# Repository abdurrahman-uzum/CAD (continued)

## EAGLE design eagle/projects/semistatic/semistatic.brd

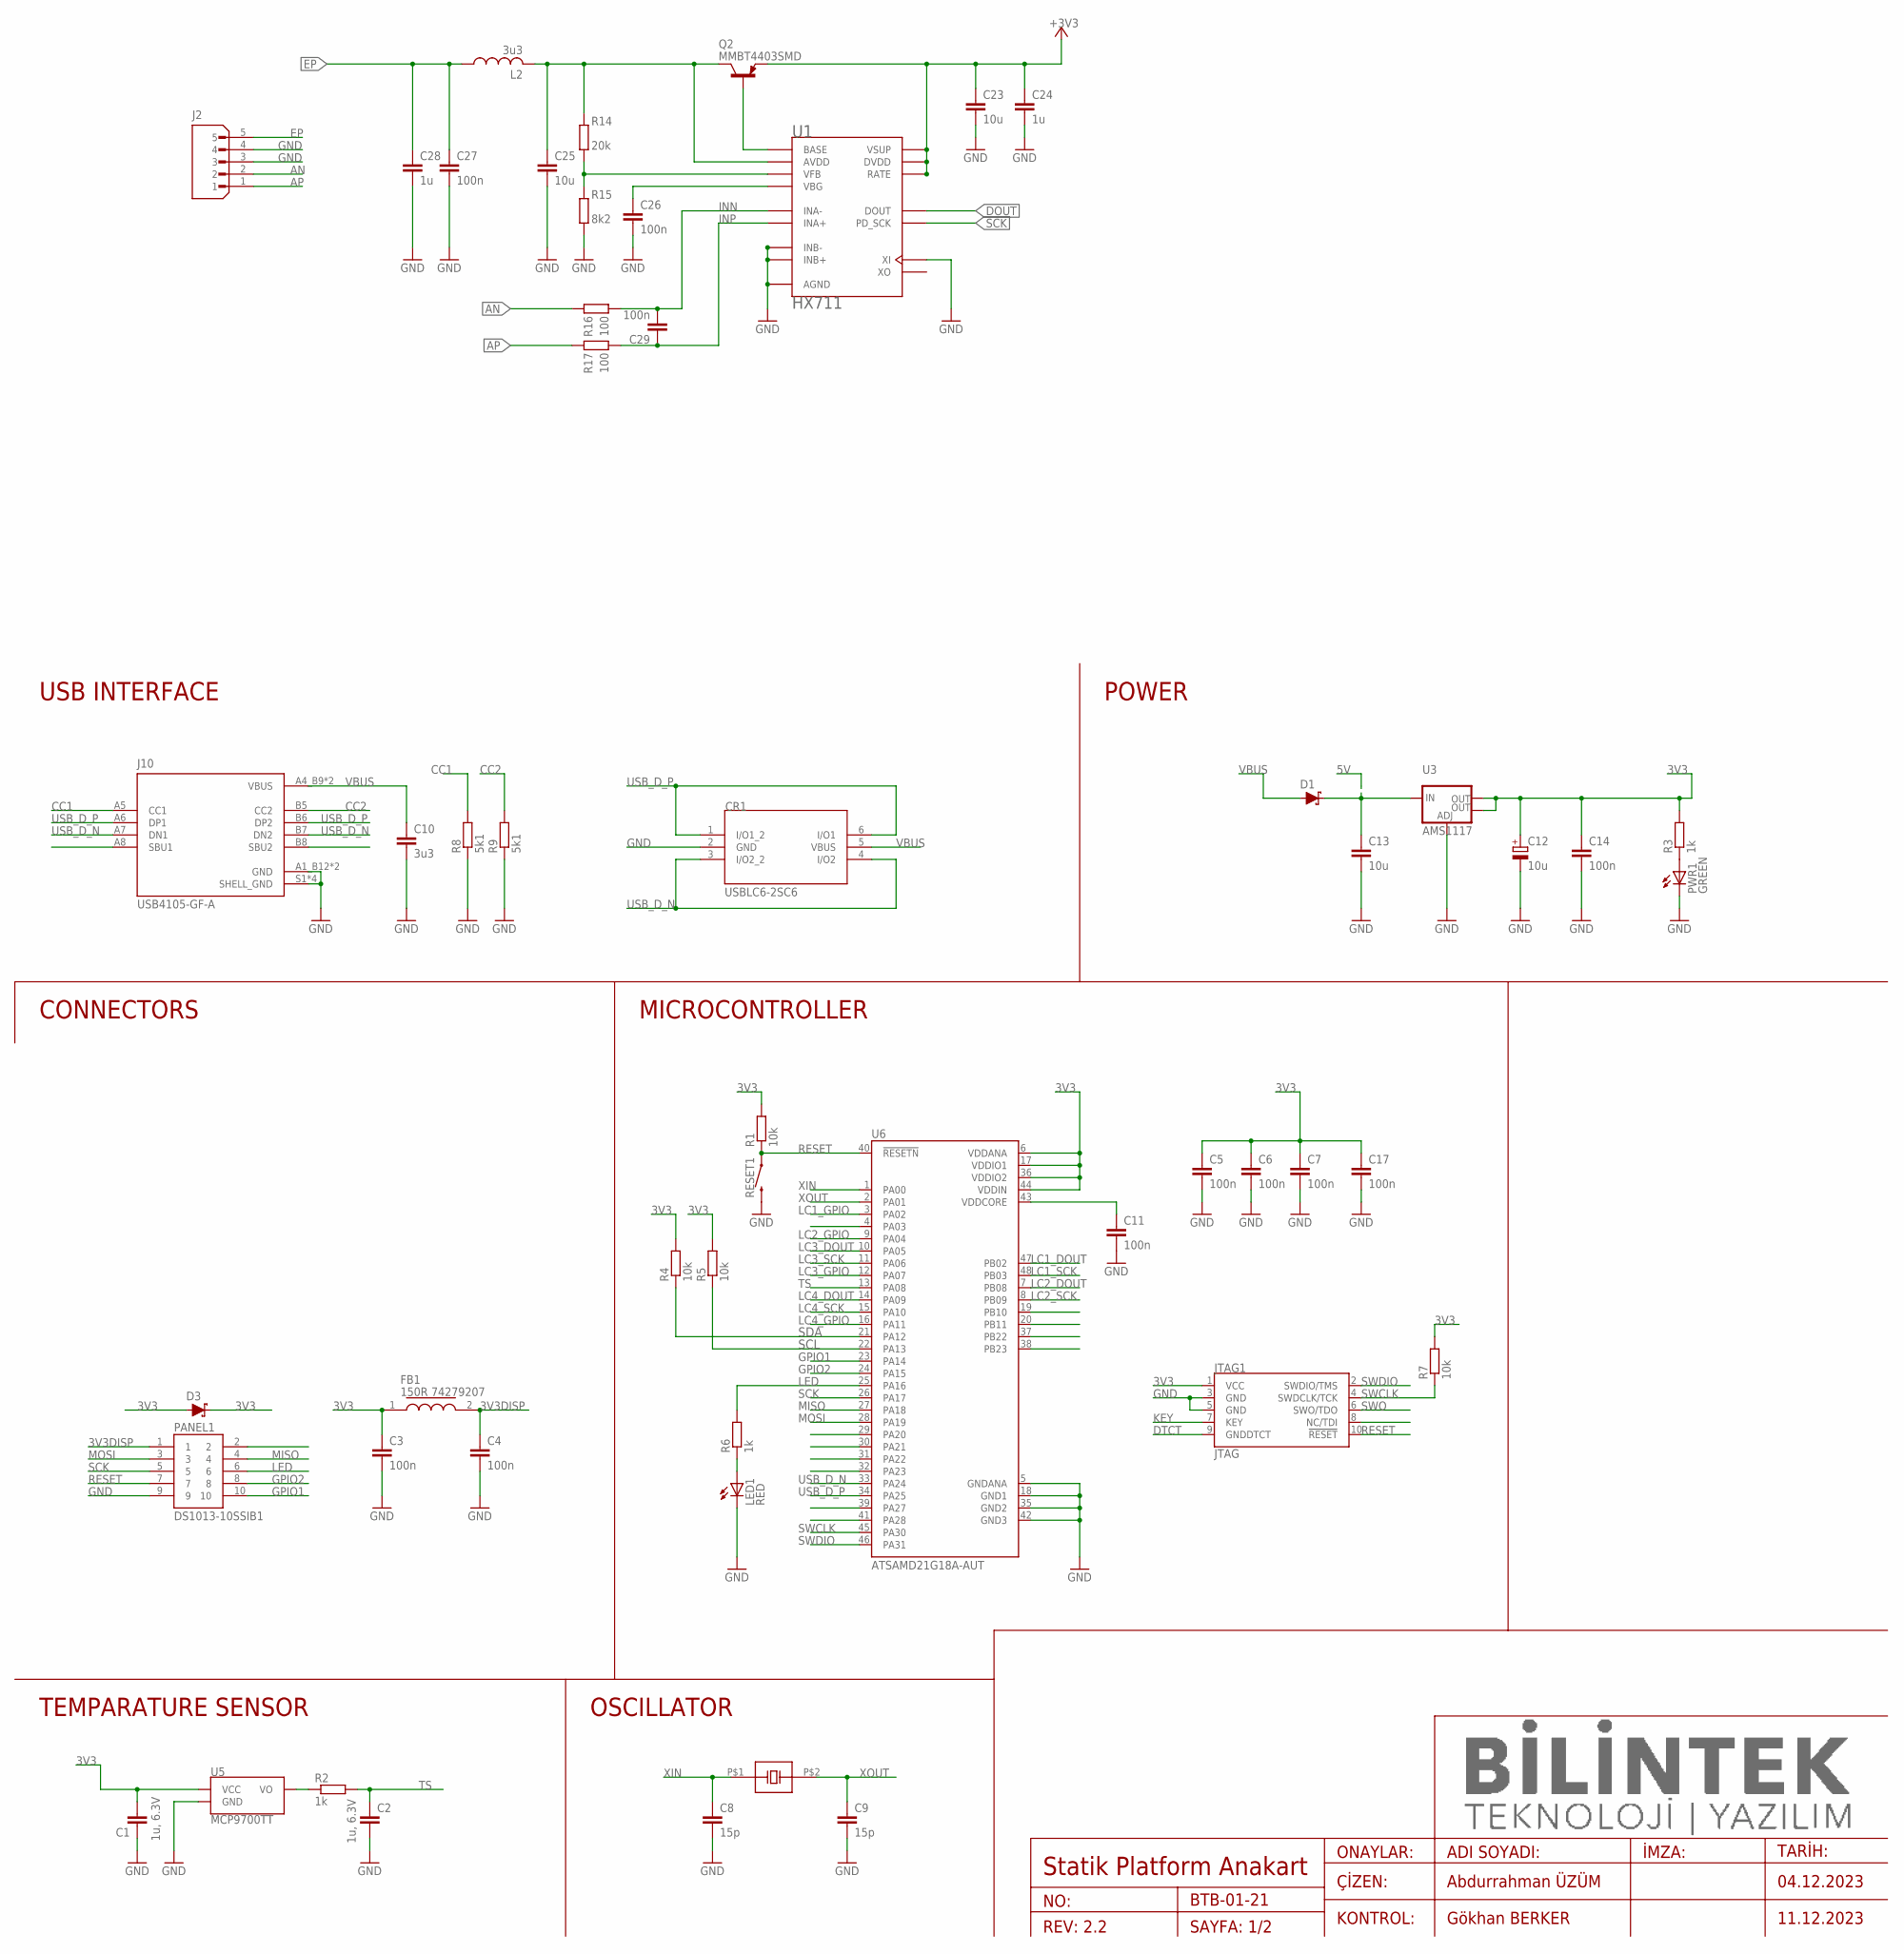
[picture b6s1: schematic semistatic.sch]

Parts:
C1, C2: 1u, 6.3V; C0603
C3, C4, C5, C6, C7, C11, C14, C17, C26, C27, C29: 100n; C0603
C8, C9: 15p; C0603
C10: 3u3; C0603K
C12: 10u; PANASONIC_D
C13, C23, C25: 10u; C0603
C24, C28: 1u; C0603
CR1: USBLC6-2SC6; SOT23-6L_STM
D1, D3: 3A/10V/280mV; SOD-323
FB1: 150R 74279207; CAPC2012X90N
J2: B5B-XH-A(LF)(SN); JST_B5B-XH-A(LF)(SN)
J10: USB4105-GF-A; GCT_USB4105-GF-A
JTAG1: JTAG; SAMTECH_FTSH-105-01
L2: 3u3; L3216C
LED1: RED; CHIPLED_0805
PANEL1: DS1013-10SSIB1; CONNFLY_DS1013-10SSIB1
PWR1: GREEN; CHIPLED_0805
Q2: MMBT4403SMD; SOT23-BEC
R1, R4, R5, R7: 10k; R0603
R2, R3, R6: 1k; R0603
R8, R9: 5k1; R0603
R14: 20k; R0603
R15: 8k2; R0603
R16, R17: 100; R0603
RESET1: MOMENTARY-SWITCH-SPST-SMD-6.0X3.5MM; TACTILE_SWITCH_SMD_6.0X3.5MM
U1: HX711; SOP127P600X180-16N
U3: AMS1117; SOT223
U5: MCP9700TT; SOT23-3
U6: ATSAMD21G18A-AUT; QFP50P900X900X120-48N
Y2: 32728; CRYSTALSAMD

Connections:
3V3: C1.2, C3.1, C5.1, C6.1, C7.1, C12.+, C14.1, C17.1, D3.A, D3.C, FB1.1, JTAG1.1 (VCC), R1.2, R3.2, R4.2, R5.2, R7.2, U3.2 (OUT), U3.4 (OUT), U5.1 (VCC), U6.6 (VDDANA), U6.17 (VDDIO1), U6.36 (VDDIO2), U6.44 (VDDIN)
3V3DISP: C4.1, FB1.2, PANEL1.1
5V: C13.1, D1.C, U3.3 (IN)
+3V3: C23.1, C24.1, Q2.E, U1.1 (VSUP), U1.15 (RATE), U1.16 (DVDD)
AN: J2.2, R16.2
AP: J2.1, R17.2
AVDD1: C25.1, L2.2, Q2.C, R14.1, U1.3 (AVDD)
BASE1: Q2.B, U1.2 (BASE)
CC1: J10.A5 (CC1), R8.2
CC2: J10.B5 (CC2), R9.2
DOUT: U1.12 (DOUT)
DTCT: JTAG1.9 (GNDDTCT)
EP: C27.1, C28.1, J2.5, L2.1
GND: C1.1, C2.2, C3.2, C4.2, C5.2, C6.2, C7.2, C8.2, C9.2, C10.2, C11.2, C12.-, C13.2, C14.2, C17.2, C23.2, C24.2, C25.2, C26.2, C27.2, C28.2, CR1.2 (GND), J2.3, J2.4, J10.A1_B12 (GND), J10.B1_A12 (GND), J10.S1 (SHELL_GND), J10.S2 (SHELL_GND), J10.S3 (SHELL_GND), J10.S4 (SHELL_GND), JTAG1.3 (GND), JTAG1.5 (GND), LED1.C, PANEL1.9, PWR1.C, R8.1, R9.1, R15.2, RESET1.2, U1.5 (AGND), U1.9 (INB-), U1.10 (INB+), U1.14 (XI), U3.1 (ADJ), U5.3 (GND), U6.5 (GNDANA), U6.18 (GND1), U6.35 (GND2), U6.42 (GND3)
GPIO1: PANEL1.10, U6.23 (PA14)
GPIO2: PANEL1.8, U6.24 (PA15)
INN: C29.2, R16.1, U1.7 (INA-)
INP: C29.1, R17.1, U1.8 (INA+)
KEY: JTAG1.7 (KEY)
LC1_DOUT: U6.47 (PB02)
LC1_GPIO: U6.3 (PA02)
LC1_SCK: U6.48 (PB03)
LC2_DOUT: U6.7 (PB08)
LC2_GPIO: U6.9 (PA04)
LC2_SCK: U6.8 (PB09)
LC3_DOUT: U6.10 (PA05)
LC3_GPIO: U6.12 (PA07)
LC3_SCK: U6.11 (PA06)
LC4_DOUT: U6.14 (PA09)
LC4_GPIO: U6.16 (PA11)
LC4_SCK: U6.15 (PA10)
LED: PANEL1.6, R6.2, U6.25 (PA16)
LED_GP2: LED1.A, R6.1
LED_PWR1: PWR1.A, R3.1
MISO: PANEL1.4, U6.27 (PA18)
MOSI: PANEL1.3, U6.28 (PA19)
unnamed: R2.1, U5.2 (VO)
RESET: JTAG1.10 (!RESET), PANEL1.7, R1.1, RESET1.1, U6.40 (!RESETN)
SCK: PANEL1.5, U1.11 (PD_SCK), U6.26 (PA17)
SCL: R5.1, U6.22 (PA13)
SDA: R4.1, U6.21 (PA12)
SWCLK: JTAG1.4 (SWDCLK/TCK), R7.1, U6.45 (PA30)
SWDIO: JTAG1.2 (SWDIO/TMS), U6.46 (PA31)
SWO: JTAG1.6 (SWO/TDO)
TS: C2.1, R2.2, U6.13 (PA08)
USB_D_N: CR1.3 (I/O2_2), CR1.4 (I/O2), J10.A7 (DN1), J10.B7 (DN2), U6.33 (PA24)
USB_D_P: CR1.1 (I/O1_2), CR1.6 (I/O1), J10.A6 (DP1), J10.B6 (DP2), U6.34 (PA25)
VBG1: C26.1, U1.6 (VBG)
VBUS: C10.1, CR1.5 (VBUS), D1.A, J10.A4_B9 (VBUS), J10.B4_A9 (VBUS)
VDDCORE1: C11.1, U6.43 (VDDCORE)
VFB1: R14.2, R15.1, U1.4 (VFB)
XIN: C8.1, U6.1 (PA00), Y2.P$1 (XIN)
XOUT: C9.1, U6.2 (PA01), Y2.P$2 (XOUT)

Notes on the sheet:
Statik Platform Anakart
REV: 2.2
SAYFA: 1/2
ONAYLAR:
ÇİZEN:
KONTROL:
ADI SOYADI:
TARİH:
Abdurrahman ÜZÜM
Gökhan BERKER
04.12.2023
11.12.2023
BTB-01-21
NO:
İMZA:
USB INTERFACE
POWER
CONNECTORS
MICROCONTROLLER
TEMPARATURE SENSOR
OSCILLATOR

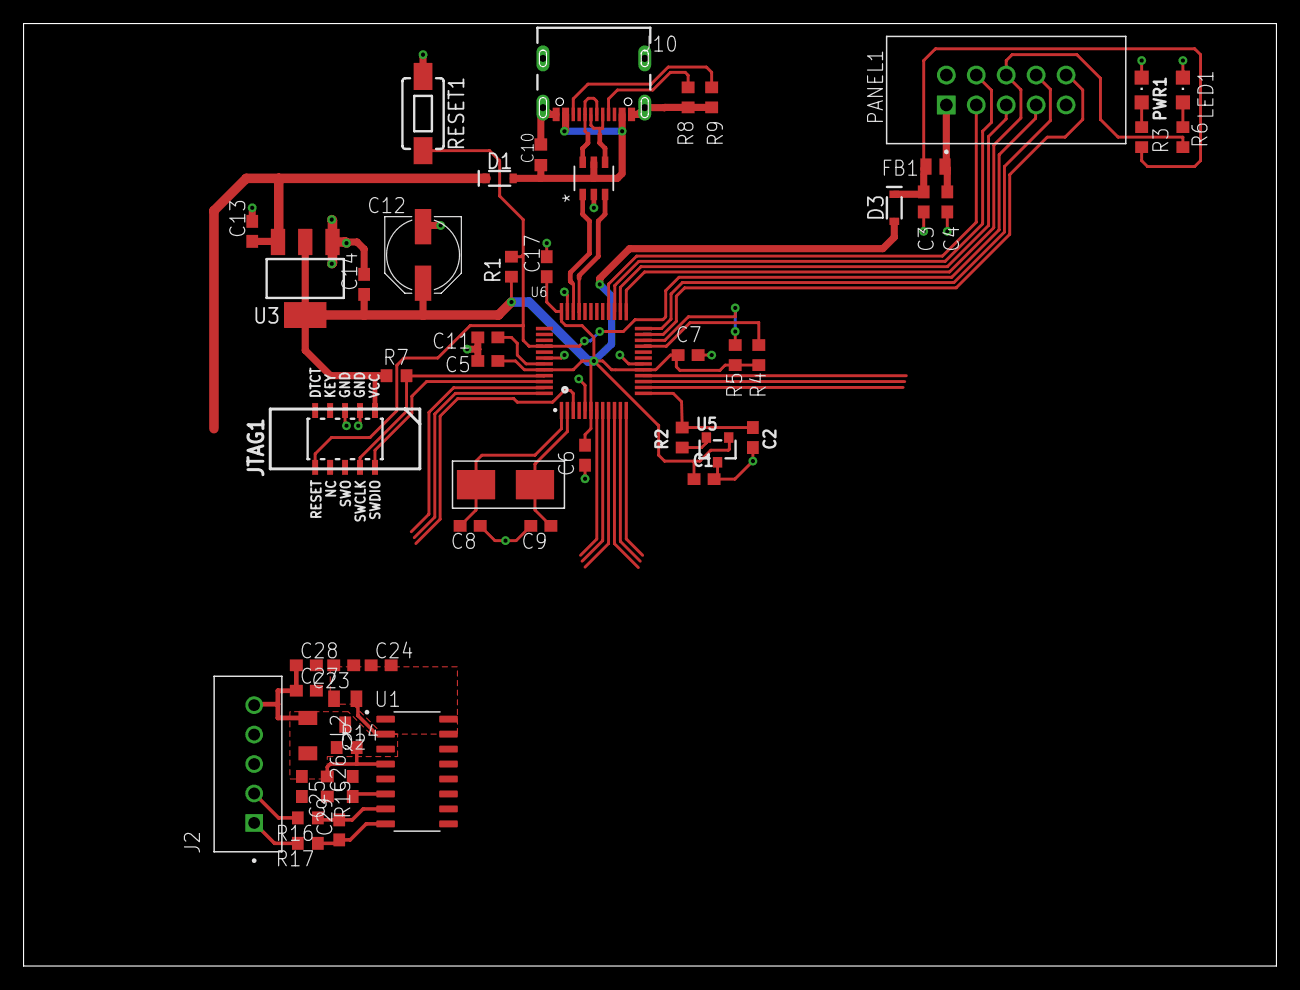
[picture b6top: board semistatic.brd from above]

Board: 2 copper layers, 106.3 x 80.0 mm, 53 parts (0 on the bottom side), 37 nets.
